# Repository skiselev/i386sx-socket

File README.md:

# i386sx-socket
386SX Universal Socket Adapter for the [Alsea River 386SX Motherboard](https://github.com/skiselev/mb386sx-rc2016)

## Hardware Documentation

### Schematic and PCB Layout

* [Schematic - Version 1.0](KiCad/i386sx-socket-Schematic-1.0.pdf)
* [PCB Layout - Version 1.0](KiCad/i386sx-socket-Board-1.0.pdf)

### Jumpers

#### JP1, JP2 - Bypass the 3.3V Voltage Regulator

Position         | Description
-----------------|--------------------------------------------------------------------------------------------------
Closed (default) | 5V CPU: 5V from the socket is connected to the CPU VCC pins, bypassing the 3.3V voltage regulator
Open             | 3.3V CPU: CPU VCC pins are connected to the 3.3V voltage regulator

#### JP3 - Connect Pin 45 to VCC

Position         | Description
-----------------|--------------------------------------------------------------------------------------------------
1-2              | 5V CPU: Socket pin 45 is connected to the CPU pin 45
Open             | 3.3V CPU: CPU pin 45 is connected to 5V (VCC5 for the 3.3V CPUs)

### Bill of Materials

#### Version 1.0

[386SX Universal Socket Adapter project on Mouser.com](https://www.mouser.com/Tools/Project/Share?AccessID=3e806c1828) - View and order most components except of the CPU, and the PCB.

Component type     | Reference | Description                                          | Quantity | Possible sources and notes 
------------------ | --------- | ---------------------------------------------------- | -------- | --------------------------
PCB                |           | 386SX Universal Socket PCB - Version 1.0             | 1        | Order from a PCB manufacturer of your choice using provided Gerber or KiCad files
Integrated Circuit | U1        | 386SX CPU, TI486SXLC, Cx486SLC CPU, 100 pin BQFP     | 1        | eBay
Integrated Circuit | U2        | NCP1117-3.3, 3.3 V LDO voltge regulator, TO-252-3    | 1        | Mouser [863-NCP1117DT33T5G](https://www.mouser.com/ProductDetail/863-NCP1117DT33T5G). Optional - required for 3.3V CPU
Capacitor          | C1 - C3   | 100 nF, MLCC, 0603 SMD                               | 3        | Mouser [581-KGM15BR71H104JM](https://www.mouser.com/ProductDetail/581-KGM15BR71H104JM). C3 is optional - required for 3.3V CPU
Capacitor          | C4, C5    | 10 uF, MLCC or Tantalum, 1206 SMD                    | 2        | Mouser [963-TMK316BJ106KL-T](https://www.mouser.com/ProductDetail/963-TMK316BJ106KL-T), [74-T55A106M6R3C0200](https://www.mouser.com/ProductDetail/74-T55A106M6R3C0200). Optional - required for 3.3V CPU
Connector          | J1 - J4   | 2x13 pin header, 2 mm pitch                          | 4        | Mouser [538-87758-2616](https://www.mouser.com/ProductDetail/538-87758-2616), [200-MTMM11305LD190](https://www.mouser.com/ProductDetail/200-MTMM11305LD190)

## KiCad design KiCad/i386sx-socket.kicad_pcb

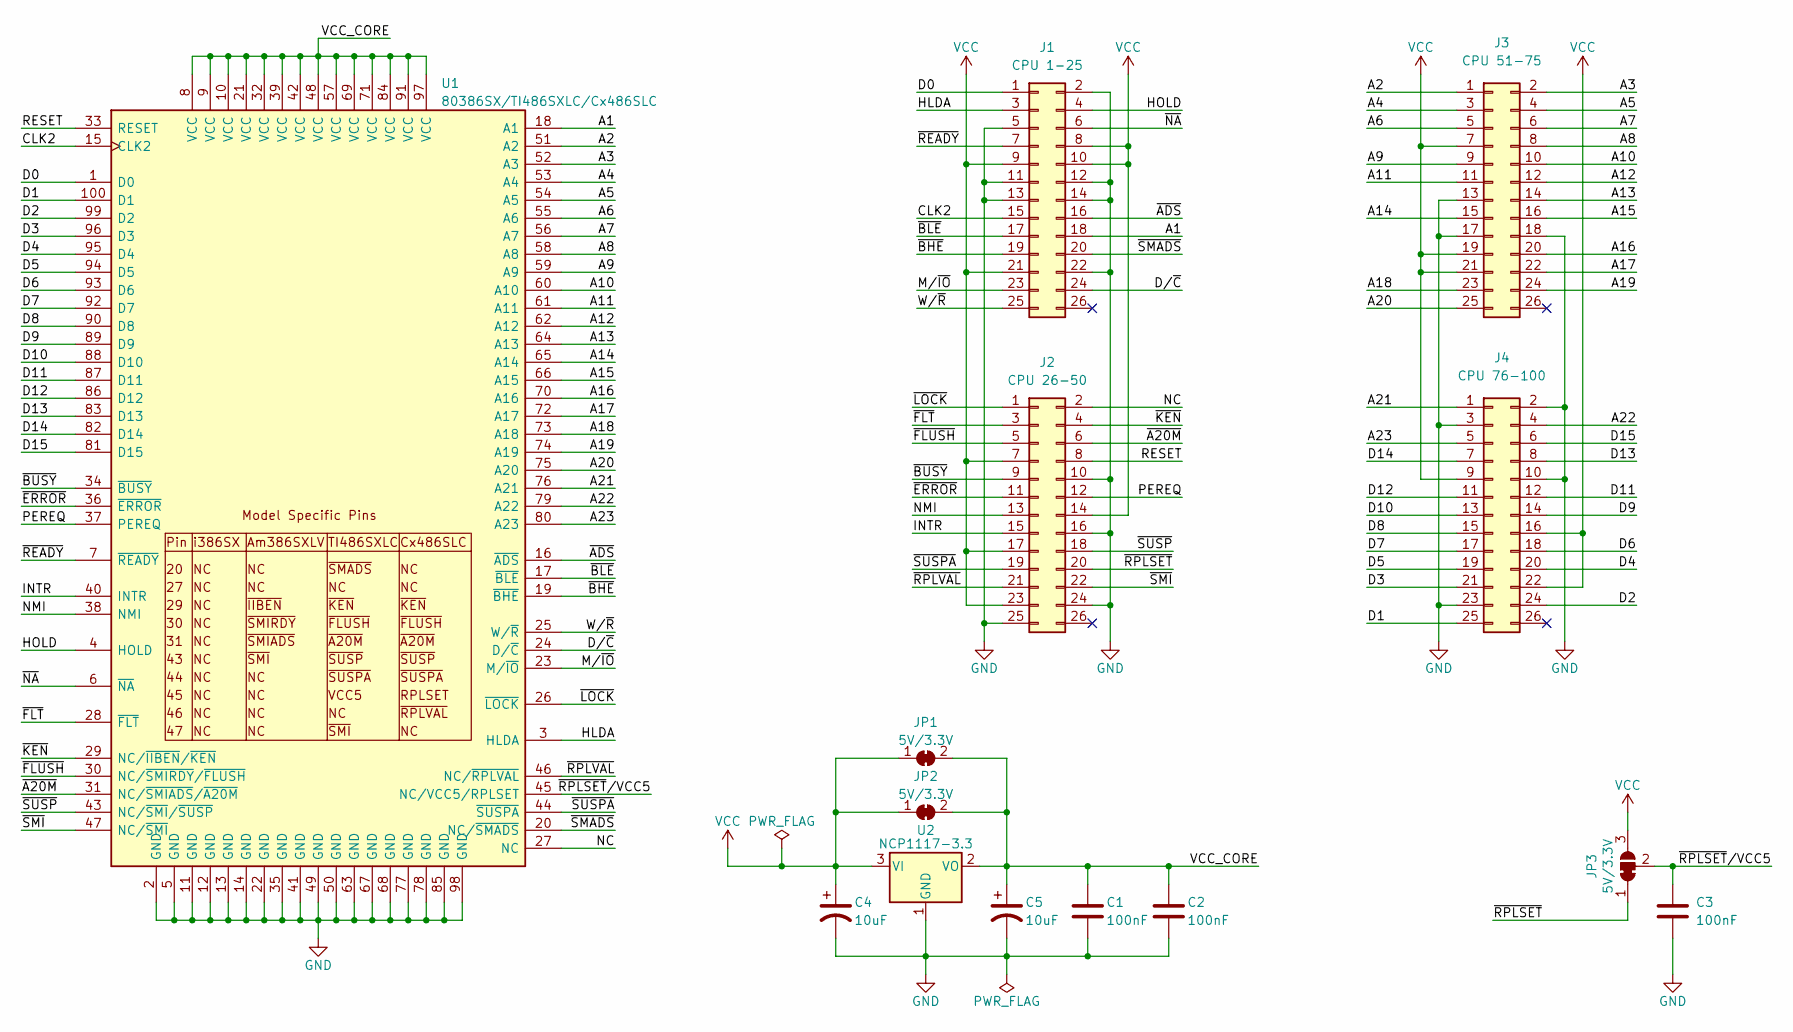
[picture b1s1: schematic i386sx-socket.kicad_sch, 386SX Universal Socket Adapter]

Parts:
C1, C2, C3: 100nF; C_0603_1608Metric_Pad1.08x0.95mm_HandSolder
C4, C5: 10uF; C_1206_3216Metric_Pad1.33x1.80mm_HandSolder
J1: CPU 1-25; PinHeader_2x13_P2.00mm_Vertical
J2: CPU 26-50; PinHeader_2x13_P2.00mm_Vertical
J3: CPU 51-75; PinHeader_2x13_P2.00mm_Vertical
J4: CPU 76-100; PinHeader_2x13_P2.00mm_Vertical
JP1, JP2: 5V/3.3V; SolderJumper-2_P1.3mm_Bridged2Bar_RoundedPad1.0x1.5mm
JP3: 5V/3.3V; SolderJumper-3_P1.3mm_Bridged2Bar12_RoundedPad1.0x1.5mm_Num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
U1: 80386SX/TI486SXLC/Cx486SLC; PQFP-100_19x19mm_P0.635mm_i386sx
U2: NCP1117-3.3; TO-252-2

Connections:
/A1: J1.18, U1.18 (A1)
/A2: J3.1, U1.51 (A2)
/A3: J3.2, U1.52 (A3)
/A4: J3.3, U1.53 (A4)
/A5: J3.4, U1.54 (A5)
/A6: J3.5, U1.55 (A6)
/A7: J3.6, U1.56 (A7)
/A8: J3.8, U1.58 (A8)
/A9: J3.9, U1.59 (A9)
/A10: J3.10, U1.60 (A10)
/A11: J3.11, U1.61 (A11)
/A12: J3.12, U1.62 (A12)
/A13: J3.14, U1.64 (A13)
/A14: J3.15, U1.65 (A14)
/A15: J3.16, U1.66 (A15)
/A16: J3.20, U1.70 (A16)
/A17: J3.22, U1.72 (A17)
/A18: J3.23, U1.73 (A18)
/A19: J3.24, U1.74 (A19)
/A20: J3.25, U1.75 (A20)
/A21: J4.1, U1.76 (A21)
/A22: J4.4, U1.79 (A22)
/A23: J4.5, U1.80 (A23)
/CLK2: J1.15, U1.15 (CLK2)
/D0: J1.1, U1.1 (D0)
/D1: J4.25, U1.100 (D1)
/D2: J4.24, U1.99 (D2)
/D3: J4.21, U1.96 (D3)
/D4: J4.20, U1.95 (D4)
/D5: J4.19, U1.94 (D5)
/D6: J4.18, U1.93 (D6)
/D7: J4.17, U1.92 (D7)
/D8: J4.15, U1.90 (D8)
/D9: J4.14, U1.89 (D9)
/D10: J4.13, U1.88 (D10)
/D11: J4.12, U1.87 (D11)
/D12: J4.11, U1.86 (D12)
/D13: J4.8, U1.83 (D13)
/D14: J4.7, U1.82 (D14)
/D15: J4.6, U1.81 (D15)
/D/~C: J1.24, U1.24 (D/~C)
/HLDA: J1.3, U1.3 (HLDA)
/HOLD: J1.4, U1.4 (HOLD)
/INTR: J2.15, U1.40 (INTR)
/M/~IO: J1.23, U1.23 (M/~IO)
/NC: J2.2, U1.27 (NC)
/NMI: J2.13, U1.38 (NMI)
/PEREQ: J2.12, U1.37 (PEREQ)
/RESET: J2.8, U1.33 (RESET)
/VCC_CORE: C1.1, C2.1, C5.1, JP1.2 (B), JP2.2 (B), U1.8 (VCC), U1.9 (VCC), U1.10 (VCC), U1.21 (VCC), U1.32 (VCC), U1.39 (VCC), U1.42 (VCC), U1.48 (VCC), U1.57 (VCC), U1.69 (VCC), U1.71 (VCC), U1.84 (VCC), U1.91 (VCC), U1.97 (VCC), U2.2 (VO)
/W/~R: J1.25, U1.25 (W/~R)
/~A20M: J2.6, U1.31 (NC/~SMIADS/~A20M)
/~ADS: J1.16, U1.16 (~ADS)
/~BHE: J1.19, U1.19 (~BHE)
/~BLE: J1.17, U1.17 (~BLE)
/~BUSY: J2.9, U1.34 (~BUSY)
/~ERROR: J2.11, U1.36 (~ERROR)
/~FLT: J2.3, U1.28 (~FLT)
/~FLUSH: J2.5, U1.30 (NC/~SMIRDY/~FLUSH)
/~KEN: J2.4, U1.29 (NC/~IIBEN/~KEN)
/~LOCK: J2.1, U1.26 (~LOCK)
/~NA: J1.6, U1.6 (~NA)
/~READY: J1.7, U1.7 (~READY)
/~RPLSET: J2.20, JP3.1 (A)
/~RPLSET/VCC5: C3.1, JP3.2 (C), U1.45 (NC/VCC5/RPLSET)
/~RPLVAL: J2.21, U1.46 (NC/~RPLVAL)
/~SMADS: J1.20, U1.20 (NC/~SMADS)
/~SMI: J2.22, U1.47 (NC/~SMI)
/~SUSPA: J2.19, U1.44 (~SUSPA)
/~SUSP: J2.18, U1.43 (NC/~SMI/~SUSP)
GND: C1.2, C2.2, C3.2, C4.2, C5.2, J1.2, J1.5, J1.11, J1.12, J1.13, J1.14, J1.22, J2.10, J2.16, J2.24, J2.25, J3.13, J3.17, J3.18, J4.2, J4.3, J4.10, J4.23, U1.2 (GND), U1.5 (GND), U1.11 (GND), U1.12 (GND), U1.13 (GND), U1.14 (GND), U1.22 (GND), U1.35 (GND), U1.41 (GND), U1.49 (GND), U1.50 (GND), U1.63 (GND), U1.67 (GND), U1.68 (GND), U1.77 (GND), U1.78 (GND), U1.85 (GND), U1.98 (GND), U2.1 (GND)
VCC: C4.1, J1.8, J1.9, J1.10, J1.21, J2.7, J2.14, J2.17, J2.23, J3.7, J3.19, J3.21, J4.9, J4.16, J4.22, JP1.1 (A), JP2.1 (A), JP3.3 (B), U2.3 (VI)

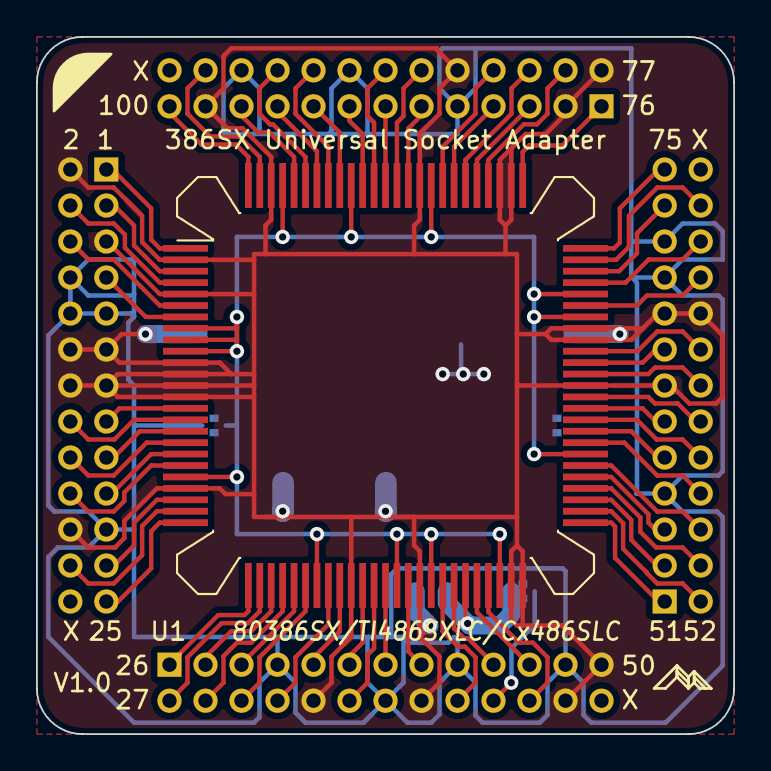
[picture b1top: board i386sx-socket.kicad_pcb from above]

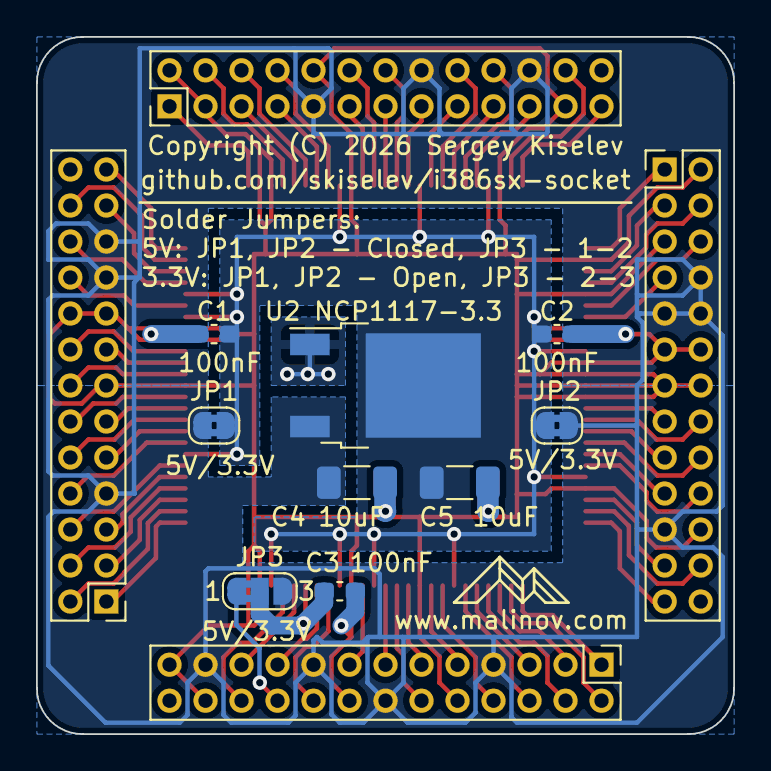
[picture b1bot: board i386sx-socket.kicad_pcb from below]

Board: 2 copper layers, 38.7 x 38.7 mm, 14 parts (13 on the bottom side), 72 nets.

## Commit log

2026-01-28 Add version 1.0 files
2026-01-28 Make PCB slightly larger so that zones connect on the outside edge
2026-02-17 README: Update links in the BoM
2026-02-17 Add pictures
2026-02-17 README: Add pictures

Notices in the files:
KiCad/i386sx-socket.kicad_pcb:
Copyright (C) 2026 Sergey Kiselev
